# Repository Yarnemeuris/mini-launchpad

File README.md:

# mini-launchpad

Mini launchpad is a midi devicde and control surface for Ableton. When connected to a computer it can: send midi notes, start and stop clips, be used as audio output, change the volume and change paramaters. When not connected to a computer it can: play notes and create sound with a synth.

## connected to Ableton

Mini launchpad is specificy designed to be used with Ableton Live. When you connect it to a computer, it uses an internal usb hub so you can use it as an audio output and send commands through Ableton. When connected it can be used as a midi keyboard or start and stop cilps in the session view.

## standalone

When mini launchpad is in standalone mode, you can only use the midi keyboard. This will send midi into a synthesizer, which will then play sound. The syth can be customized a bit via the encoders at the top, but you can customize it fully if you reprogram the pi.

## compontents

Mini Launchpad has an 8x8 grid of buttons, wired to 4 io expanders. There are also 8 encoders connected to another io expander. The io expanders are used so that the microcontroller doesn't have to poll for changes, but that it can use interupts instead. This way every button press will be registerd and you can press every button at the same time. There are also some extra controll buttons and lights that are wired directly to the microcontroller. But these will also use interupt.

For audio there is a PCM5100 I²S DAC. This will convert the digital audio to a line output. Then there is an amplifier that amplifies the sound. You can also just use the line out.

## playing notes

Actually playing notes is a big part of the luanchpad. There are 2 ways to do this.
- Option 1 is that the notes are layed out linearly. This means that in the bottom left corner is a C, moving right goes up a note and moving up goes up an octave. You can change the octave of the rows by moving up and down. This is also the default option when the launchpad boots up. It looks like this:

- Option 2 is for the notes to be layed out in a c scale. The bottom left note is still a C and going right still goes up a note. But going up goes up a fourth instead of an octave. This layout is the default layout on the Ableton Push and lloks like this:

## progress

The current progress.

- [x] Design the schematic.
- [x] Design the pcb.
- [x] Design the case.
- [x] Write the firmware.

I know not a lot of the features I talk about aren't implemented yet. But for SoM those won't be included. This is beacuse mini midi magic started pretty late and it doesn't really have an end date yet. So by the end of mini midi magic this will all be implemented. The current features that aren't implemented are:
- Connecting to Ableton Live.
- Playing and controlling things in Ableton Live.
- Having a more complex and better synthesizer.
- Being able to change the synthesizer.
- Using the launchpad as an audio interface.
- And I might even add more features.

  I am also unsure if any of the code works and if the case is fully correct. Because I don't have the physical board myself. This will also change before the end of mini midi magic.

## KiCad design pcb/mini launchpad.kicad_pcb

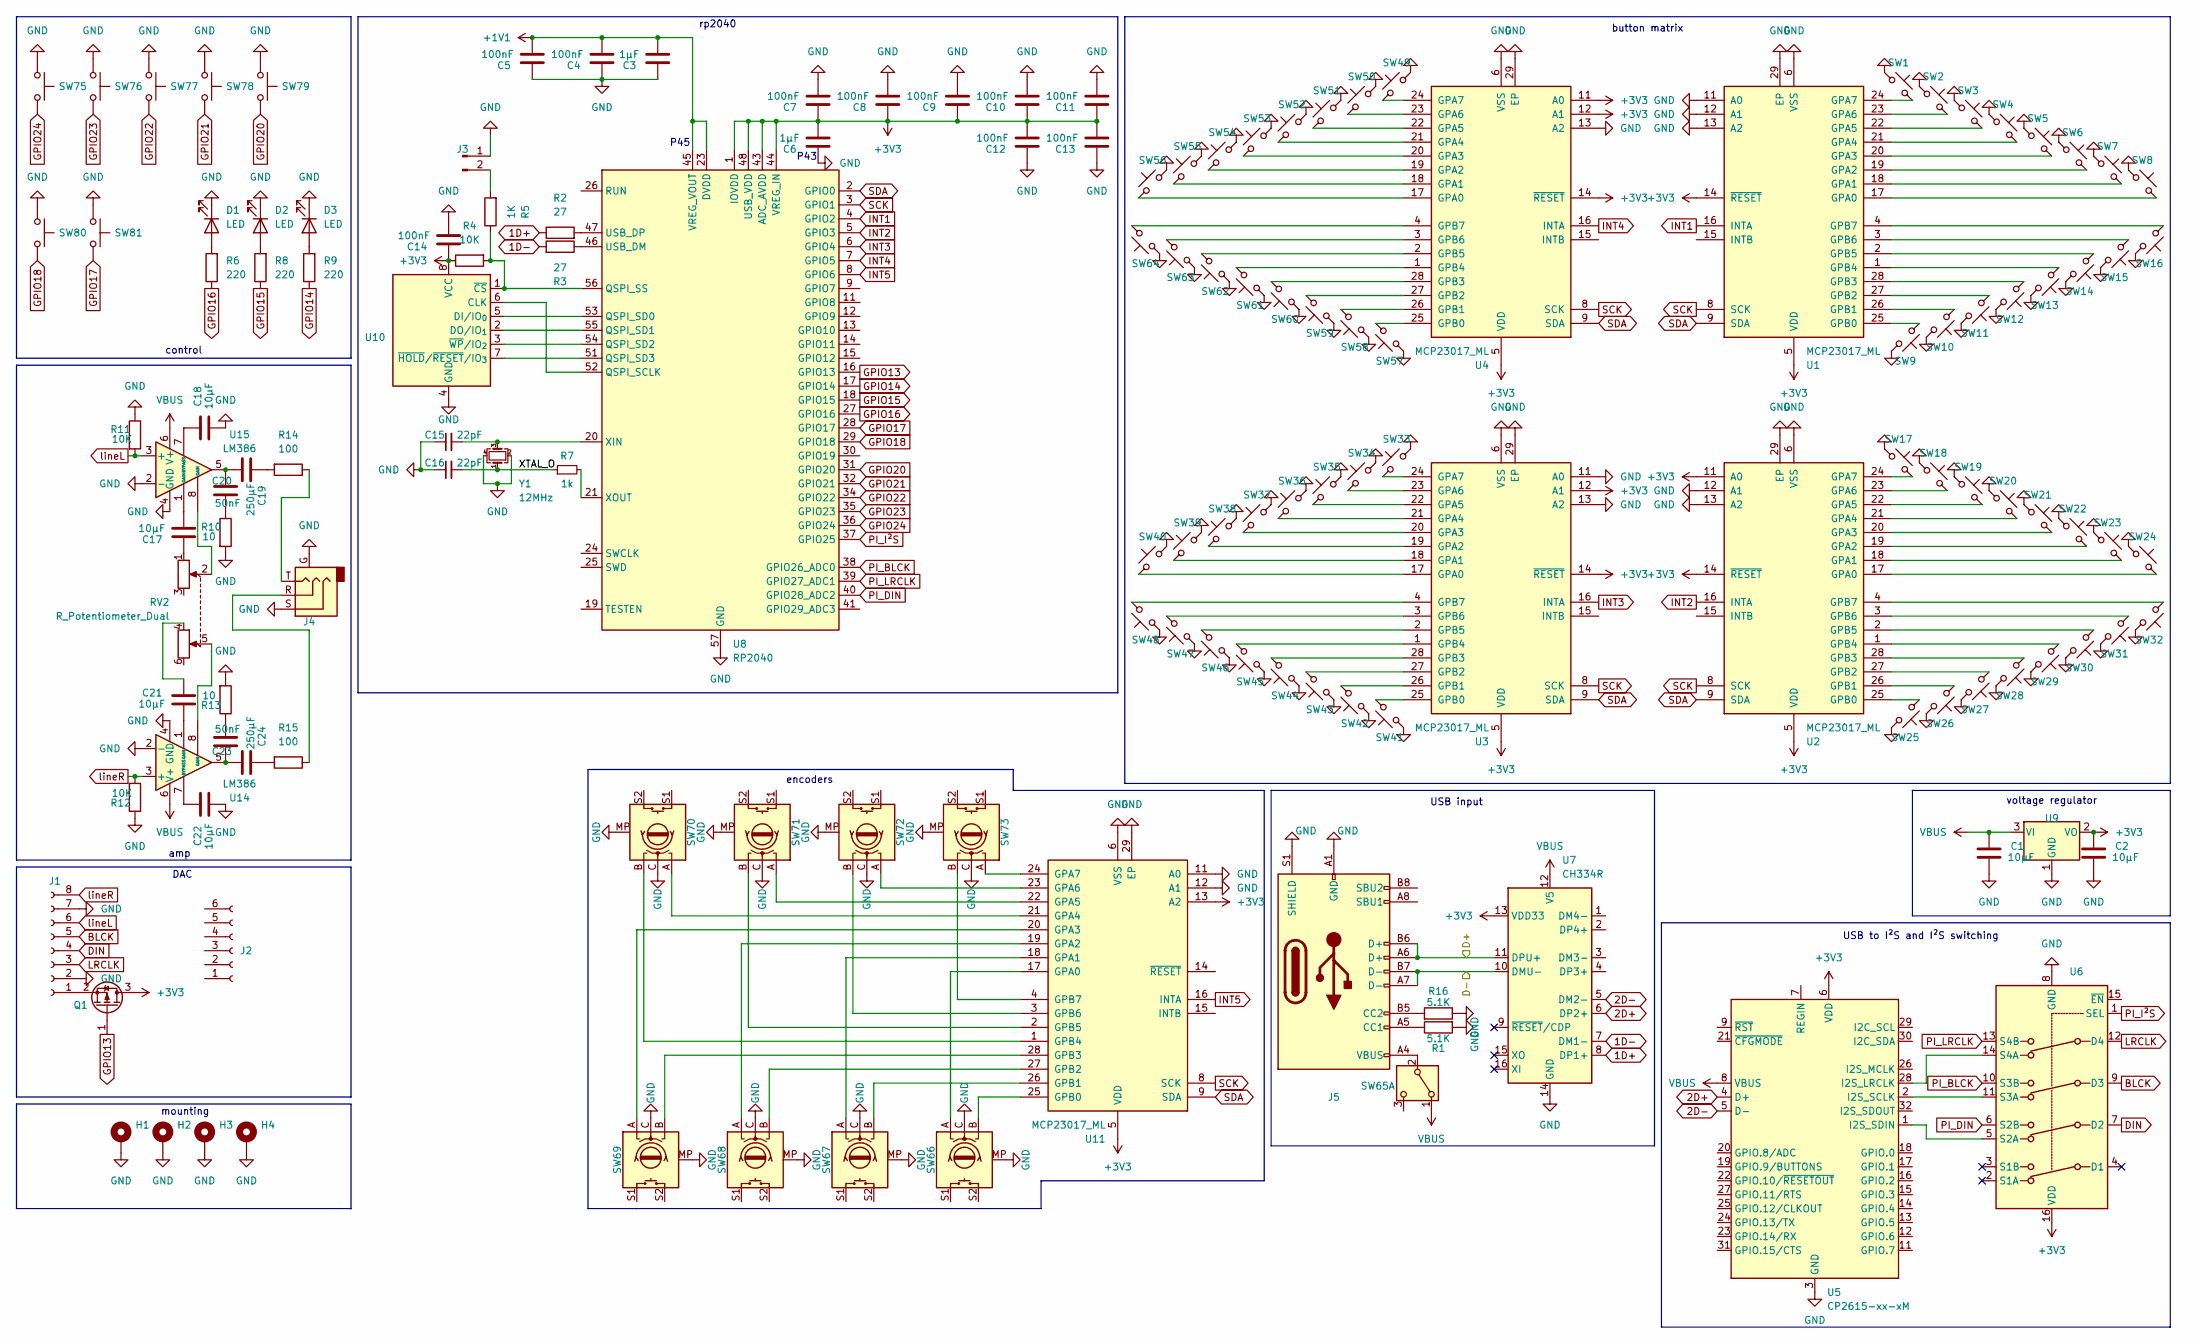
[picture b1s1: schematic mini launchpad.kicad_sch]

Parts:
C1, C2, C17, C18, C21, C22: 10µF; C_0805_2012Metric; LCSC Part C15850
C3, C6: 1µF; C_0805_2012Metric; LCSC Part C28323
C4, C5, C7, C8, C9, C10, C11, C12, C13, C14: 100nF; C_0805_2012Metric; LCSC Part C476766
C15, C16: 22pF; C_0805_2012Metric; LCSC C1804
C19, C24: 250µF; C_1206_3216Metric; LCSC Part C412252
C20, C23: 50nF; C_0805_2012Metric; LCSC Part C107154
D1, D2, D3: LED; LED_D3.0mm; LCSC Part C3028820
H1, H2, H3, H4: MountingHole_Pad; MountingHole_3.2mm_M3_Pad_TopOnly
J1: Conn_01x08_Socket; PinHeader_1x08_P2.54mm_Vertical; LCSC part C492407
J2: Conn_01x06_Socket; PinHeader_1x06_P2.54mm_Vertical; LCSC Part C5383115
J3: Conn_01x02_Pin; PinHeader_1x02_P2.54mm_Horizontal; LCSC Part C42431827
J4: AudioJack3_Ground; Jack_3.5mm_CUI_SJ1-3524N_Horizontal; LCSC Part C4992816
J5: USB_C_Receptacle_USB2.0_16P; USB_C_Receptacle_G-Switch_GT-USB-7010ASV; LCSC Part C2988369
Q1: AO3401A; SOT-23; LCSC Part C15127
R1, R16: 5.1K; R_0402_1005Metric; LCSC Part C105872
R2, R3: 27; R_0402_1005Metric; LCSC Part C138021
R4, R11, R12: 10K; R_0402_1005Metric
R5: 1K; R_0402_1005Metric; LCSC Part C11702
R6, R8, R9: 220; R_0402_1005Metric; LCSC Part C112291
R7: 1k; R_0402_1005Metric; LCSC C11702
R10, R13: 10; R_0402_1005Metric; LCSC Part C138066
R14, R15: 100; R_0402_1005Metric; LCSC Part C106232
RV2: R_Potentiometer_Dual; Potentiometer_Alpha_RD902F-40-00D_Dual_Vertical; LCSC Part C470285
SW1, SW2, SW3, SW4, SW5, SW6, SW7, SW8, SW9, SW10, SW11, SW12, SW13, SW14, SW15, SW16, SW17, SW18, SW19, SW20, SW21, SW22, SW23, SW24, SW25, SW26, SW27, SW28, SW29, SW30, SW31, SW32, SW33, SW34, SW35, SW36, SW37, SW38, SW39, SW40, SW41, SW42, SW43, SW44, SW45, SW46, SW47, SW48, SW49, SW50, SW51, SW52, SW53, SW54, SW55, SW56, SW57, SW58, SW59, SW60, SW61, SW62, SW63, SW64: SW_Cherry_MX_1.00u_PCB
SW65: SW_DPDT_x2; SW_E-Switch_EG2219_DPDT_Angled; LCSC Part C2848873
SW66, SW67, SW68, SW69, SW70, SW71, SW72, SW73: RotaryEncoder_Switch_MP; RotaryEncoder_Alps_EC11E-Switch_Vertical_H20mm_MountingHoles; LCSC Part C202365
SW75, SW76, SW77, SW78, SW79, SW80, SW81: SW_Push; SW_Cherry_MX_1.00u_PCB
U1, U2, U3, U4, U11: MCP23017_ML; QFN-28-1EP_6x6mm_P0.65mm_EP4.25x4.25mm; LCSC Part C639770
U5: CP2615-xx-xM; QFN-32-1EP_5x5mm_P0.5mm_EP3.3x3.3mm; LCSC Part C1521596
U6: TMUX1574PW; TSSOP-16_4.4x5mm_P0.65mm; LCSC Part C2673443
U7: CH334R; QSOP-16_3.9x4.9mm_P0.635mm; LCSC Part C4154405
U8: RP2040; QFN-56-1EP_7x7mm_P0.4mm_EP3.2x3.2mm; LCSC Part C2040
U9: NCP1117-3.3_TO252; TO-252-2; LCSC Part C154606
U10: W25Q128JVS; SOIC-8_5.3x5.3mm_P1.27mm; LCSC Part C97521
U14, U15: LM386; SOIC-8_3.9x4.9mm_P1.27mm; LCSC Part C23573
Y1: 12MHz; Crystal_SMD_3225-4Pin_3.2x2.5mm; LCSC Part C9002

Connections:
1D+: R2.1, U7.8 (DP1+)
1D-: R3.2, U7.7 (DM1-)
2D+: U5.4 (D+), U7.6 (DP2+)
2D-: U5.5 (D-), U7.5 (DM2-)
+1V1: C3.1, C4.1, C5.1, U8.23 (DVDD), U8.45 (VREG_VOUT), U8.50 (DVDD)
+3V3: C2.2, C6.1, C7.2, C8.2, C9.2, C10.2, C11.2, C12.1, C13.1, C14.2, Q1.3 (D), R4.1, U1.5 (VDD), U1.14 (~RESET), U2.5 (VDD), U2.11 (A0), U2.14 (~RESET), U3.5 (VDD), U3.12 (A1), U3.14 (~RESET), U4.5 (VDD), U4.11 (A0), U4.12 (A1), U4.14 (~RESET), U5.6 (VDD), U6.16 (VDD), U7.13 (VDD33), U8.1 (IOVDD), U8.10 (IOVDD), U8.22 (IOVDD), U8.33 (IOVDD), U8.42 (IOVDD), U8.43 (ADC_AVDD), U8.44 (VREG_IN), U8.48 (USB_VDD), U8.49 (IOVDD), U9.2 (VO), U10.8 (VCC), U11.5 (VDD), U11.13 (A2)
/D+: J5.A6 (D+), J5.B6 (D+), U7.11 (DPU+)
/D-: J5.A7 (D-), J5.B7 (D-), U7.10 (DMU-)
/XTAL_O: C16.2, R7.1, Y1.1
BLCK: J1.5, U6.9 (D3)
DIN: J1.4, U6.7 (D2)
GND: C1.1, C2.1, C3.2, C4.2, C5.2, C6.2, C7.1, C8.1, C9.1, C10.1, C11.1, C12.2, C13.2, C14.1, C15.1, C16.1, C18.1, C22.1, D1.1 (K), D2.1 (K), D3.1 (K), H1.1, H2.1, H3.1, H4.1, J1.2, J1.7, J3.1, J4.G, J4.S, J5.A1 (GND), J5.A12 (GND), J5.B1 (GND), J5.B12 (GND), J5.S1 (SHIELD), R1.2, R10.2, R11.1, R12.1, R13.2, R16.1, SW1.1, SW2.1, SW3.1, SW4.1, SW5.1, SW6.1, SW7.1, SW8.1, SW9.1, SW10.1, SW11.1, SW12.1, SW13.1, SW14.1, SW15.1, SW16.1, SW17.1, SW18.1, SW19.1, SW20.1, SW21.1, SW22.1, SW23.1, SW24.1, SW25.1, SW26.1, SW27.1, SW28.1, SW29.1, SW30.1, SW31.1, SW32.1, SW33.1, SW34.1, SW35.1, SW36.1, SW37.1, SW38.1, SW39.1, SW40.1, SW41.1, SW42.1, SW43.1, SW44.1, SW45.1, SW46.1, SW47.1, SW48.1, SW49.1, SW50.1, SW51.1, SW52.1, SW53.1, SW54.1, SW55.1, SW56.1, SW57.1, SW58.1, SW59.1, SW60.1, SW61.1, SW62.1, SW63.1, SW64.1, SW66.C, SW66.MP, SW67.C, SW67.MP, SW68.C, SW68.MP, SW69.C, SW69.MP, SW70.C, SW70.MP, SW71.C, SW71.MP, SW72.C, SW72.MP, SW73.C, SW73.MP, SW75.1, SW76.1, SW77.1, SW78.1, SW79.1, SW80.1, SW81.1, U1.6 (VSS), U1.11 (A0), U1.12 (A1), U1.13 (A2), U1.29 (EP), U2.6 (VSS), U2.12 (A1), U2.13 (A2), U2.29 (EP), U3.6 (VSS), U3.11 (A0), U3.13 (A2), U3.29 (EP), U4.6 (VSS), U4.13 (A2), U4.29 (EP), U5.3 (GND), U5.33 (GND), U6.8 (GND), U7.14 (GND), U8.57 (GND), U9.1 (GND), U10.4 (GND), U11.6 (VSS), U11.11 (A0), U11.12 (A1), U11.29 (EP), U14.2 (-), U14.4 (GND), U15.2 (-), U15.4 (GND), Y1.2, Y1.4
GPIO13: Q1.1 (G), U8.16 (GPIO13)
GPIO14: R9.1, U8.17 (GPIO14)
GPIO15: R8.1, U8.18 (GPIO15)
GPIO16: R6.1, U8.27 (GPIO16)
GPIO17: SW81.2, U8.28 (GPIO17)
GPIO18: SW80.2, U8.29 (GPIO18)
GPIO20: SW79.2, U8.31 (GPIO20)
GPIO21: SW78.2, U8.32 (GPIO21)
GPIO22: SW77.2, U8.34 (GPIO22)
GPIO23: SW76.2, U8.35 (GPIO23)
GPIO24: SW75.2, U8.36 (GPIO24)
INT1: U1.16 (INTA), U8.4 (GPIO2)
INT2: U2.16 (INTA), U8.5 (GPIO3)
INT3: U3.16 (INTA), U8.6 (GPIO4)
INT4: U4.16 (INTA), U8.7 (GPIO5)
INT5: U8.8 (GPIO6), U11.16 (INTA)
LRCLK: J1.3, U6.12 (D4)
unnamed: C17.1, U15.1 (GAIN)
unnamed: C17.2, RV2.1
unnamed: C19.1, C20.1, U15.5
unnamed: C19.2, R14.2
unnamed: C20.2, R10.1
unnamed: C21.1, U14.1 (GAIN)
unnamed: C21.2, RV2.4
unnamed: C23.1, C24.1, U14.5
unnamed: C23.2, R13.1
unnamed: C24.2, R15.2
unnamed: D1.2 (A), R6.2
unnamed: D2.2 (A), R8.2
unnamed: D3.2 (A), R9.2
unnamed: J1.1, Q1.2 (S)
unnamed: J3.2, R5.2
unnamed: J4.R, R15.1
unnamed: J4.T, R14.1
unnamed: J5.A5 (CC1), R1.1
unnamed: J5.B5 (CC2), R16.2
unnamed: RV2.2, U15.8 (GAIN)
unnamed: RV2.5, U14.8 (GAIN)
unnamed: J5.A4 (VBUS), J5.A9 (VBUS), J5.B4 (VBUS), J5.B9 (VBUS), SW65.2 (B)
unnamed: SW8.2, U1.17 (GPA0)
unnamed: SW7.2, U1.18 (GPA1)
unnamed: SW6.2, U1.19 (GPA2)
unnamed: SW5.2, U1.20 (GPA3)
unnamed: SW4.2, U1.21 (GPA4)
unnamed: SW3.2, U1.22 (GPA5)
unnamed: SW2.2, U1.23 (GPA6)
unnamed: SW1.2, U1.24 (GPA7)
unnamed: SW9.2, U1.25 (GPB0)
unnamed: SW10.2, U1.26 (GPB1)
unnamed: SW11.2, U1.27 (GPB2)
unnamed: SW12.2, U1.28 (GPB3)
unnamed: SW13.2, U1.1 (GPB4)
unnamed: SW14.2, U1.2 (GPB5)
unnamed: SW15.2, U1.3 (GPB6)
unnamed: SW16.2, U1.4 (GPB7)
unnamed: SW24.2, U2.17 (GPA0)
unnamed: SW23.2, U2.18 (GPA1)
unnamed: SW22.2, U2.19 (GPA2)
unnamed: SW21.2, U2.20 (GPA3)
unnamed: SW20.2, U2.21 (GPA4)
unnamed: SW19.2, U2.22 (GPA5)
unnamed: SW18.2, U2.23 (GPA6)
unnamed: SW17.2, U2.24 (GPA7)
unnamed: SW25.2, U2.25 (GPB0)
unnamed: SW26.2, U2.26 (GPB1)
unnamed: SW27.2, U2.27 (GPB2)
unnamed: SW28.2, U2.28 (GPB3)
unnamed: SW29.2, U2.1 (GPB4)
unnamed: SW30.2, U2.2 (GPB5)
unnamed: SW31.2, U2.3 (GPB6)
unnamed: SW32.2, U2.4 (GPB7)
unnamed: SW40.2, U3.17 (GPA0)
unnamed: SW39.2, U3.18 (GPA1)
unnamed: SW38.2, U3.19 (GPA2)
unnamed: SW37.2, U3.20 (GPA3)
unnamed: SW36.2, U3.21 (GPA4)
unnamed: SW35.2, U3.22 (GPA5)
unnamed: SW34.2, U3.23 (GPA6)
unnamed: SW33.2, U3.24 (GPA7)
unnamed: SW41.2, U3.25 (GPB0)
unnamed: SW42.2, U3.26 (GPB1)
unnamed: SW43.2, U3.27 (GPB2)
unnamed: SW44.2, U3.28 (GPB3)
unnamed: SW45.2, U3.1 (GPB4)
unnamed: SW46.2, U3.2 (GPB5)
unnamed: SW47.2, U3.3 (GPB6)
unnamed: SW48.2, U3.4 (GPB7)
unnamed: SW56.2, U4.17 (GPA0)
unnamed: SW55.2, U4.18 (GPA1)
unnamed: SW54.2, U4.19 (GPA2)
unnamed: SW53.2, U4.20 (GPA3)
unnamed: SW52.2, U4.21 (GPA4)
unnamed: SW51.2, U4.22 (GPA5)
unnamed: SW50.2, U4.23 (GPA6)
unnamed: SW49.2, U4.24 (GPA7)
unnamed: SW57.2, U4.25 (GPB0)
unnamed: SW58.2, U4.26 (GPB1)
unnamed: SW59.2, U4.27 (GPB2)
unnamed: SW60.2, U4.28 (GPB3)
unnamed: SW61.2, U4.1 (GPB4)
unnamed: SW62.2, U4.2 (GPB5)
unnamed: SW63.2, U4.3 (GPB6)
unnamed: SW64.2, U4.4 (GPB7)
unnamed: U5.28 (I2S_LRCLK), U6.14 (S4A)
unnamed: U5.2 (I2S_SCLK), U6.11 (S3A)
unnamed: U5.1 (I2S_SDIN), U6.5 (S2A)
unnamed: R3.1, U8.46 (USB_DM)
unnamed: R2.2, U8.47 (USB_DP)
unnamed: C15.2, U8.20 (XIN), Y1.3
unnamed: R7.2, U8.21 (XOUT)
unnamed: U8.52 (QSPI_SCLK), U10.6 (CLK)
unnamed: U8.53 (QSPI_SD0), U10.5 (DI/IO_{0})
unnamed: U8.55 (QSPI_SD1), U10.2 (DO/IO_{1})
unnamed: R4.2, R5.1, U8.56 (QSPI_SS), U10.1 (~CS)
unnamed: U8.51 (QSPI_SD3), U10.7 (~HOLD/~RESET/IO_{3})
unnamed: U8.54 (QSPI_SD2), U10.3 (~WP/IO_{2})
unnamed: SW66.A, U11.17 (GPA0)
unnamed: SW67.A, U11.18 (GPA1)
unnamed: SW68.A, U11.19 (GPA2)
unnamed: SW69.A, U11.20 (GPA3)
unnamed: SW70.A, U11.21 (GPA4)
unnamed: SW71.A, U11.22 (GPA5)
unnamed: SW72.A, U11.23 (GPA6)
unnamed: SW73.A, U11.24 (GPA7)
unnamed: SW66.B, U11.25 (GPB0)
unnamed: SW67.B, U11.26 (GPB1)
unnamed: SW68.B, U11.27 (GPB2)
unnamed: SW69.B, U11.28 (GPB3)
unnamed: SW70.B, U11.1 (GPB4)
unnamed: SW71.B, U11.2 (GPB5)
unnamed: SW72.B, U11.3 (GPB6)
unnamed: SW73.B, U11.4 (GPB7)
unnamed: C22.2, U14.7 (BYPASS)
unnamed: C18.2, U15.7 (BYPASS)
PI_BLCK: U6.10 (S3B), U8.38 (GPIO26_ADC0)
PI_DIN: U6.6 (S2B), U8.40 (GPIO28_ADC2)
PI_I²S: U6.1 (SEL), U8.37 (GPIO25)
PI_LRCLK: U6.13 (S4B), U8.39 (GPIO27_ADC1)
SCK: U1.8 (SCK), U2.8 (SCK), U3.8 (SCK), U4.8 (SCK), U8.3 (GPIO1), U11.8 (SCK)
SDA: U1.9 (SDA), U2.9 (SDA), U3.9 (SDA), U4.9 (SDA), U8.2 (GPIO0), U11.9 (SDA)
VBUS: C1.2, SW65.1 (A), U5.8 (VBUS), U7.12 (V5), U9.3 (VI), U14.6 (V+), U15.6 (V+)
lineL: J1.6, R11.2, U15.3 (+)
lineR: J1.8, R12.2, U14.3 (+)

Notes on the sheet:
rp2040
button matrix
USB to I²S and I²S switching
P43
control
amp
mounting
DAC
encoders
USB input
voltage regulator
P45

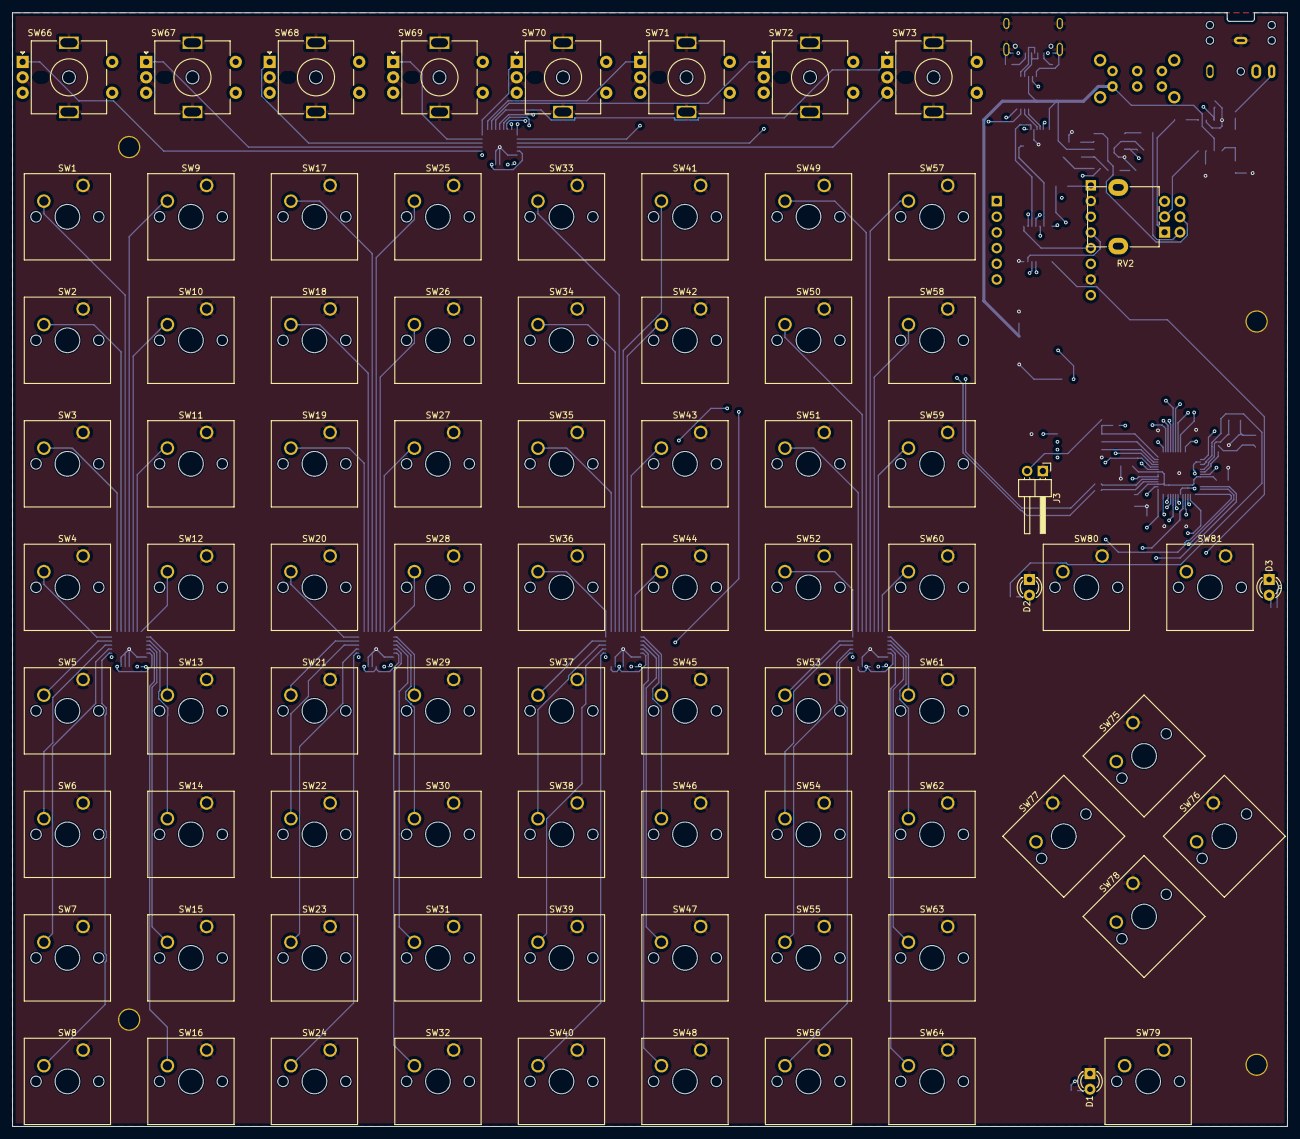
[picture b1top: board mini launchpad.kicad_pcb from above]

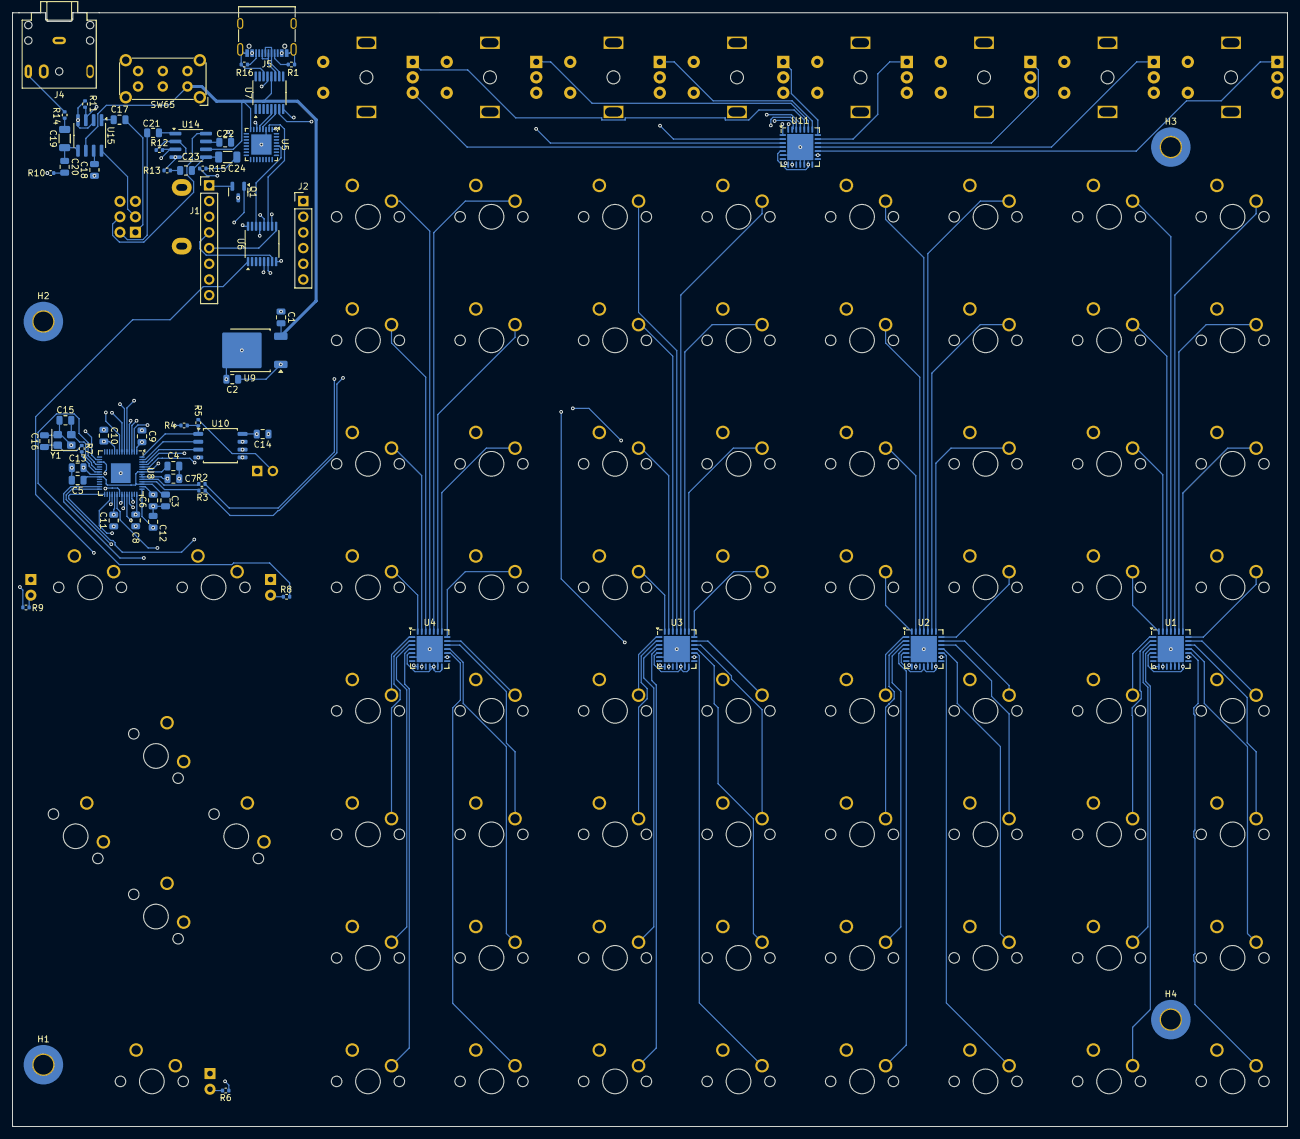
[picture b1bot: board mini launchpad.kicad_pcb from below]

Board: 4 copper layers, 206.5 x 180.3 mm, 148 parts (64 on the bottom side), 155 nets.

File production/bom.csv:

Designator,Footprint,Quantity,Value,LCSC Part #
"C1, C17, C18, C2, C21, C22",0805,6,10µF,C15850
"C10, C11, C12, C13, C14, C4, C5, C7, C8, C9",0805,10,100nF,C476766
"C15, C16",0805,2,22pF,C1804
C19,1206,1,250µF,
"C20, C23",0805,2,50nF,C107154
C24,1206,1,250µF,C412252
"C3, C6",0805,2,1µF,C28323
"D1, D2, D3",LED_D3.0mm,3,LED,C3028820
J1,PinHeader_1x08_P2.54mm_Vertical,1,Conn_01x08_Socket,
J2,PinHeader_1x06_P2.54mm_Vertical,1,Conn_01x06_Socket,C5383115
J4,Jack_3.5mm_CUI_SJ1-3524N_Horizontal,1,AudioJack3_Ground,C4992816
J5,USB_C_Receptacle_G-Switch_GT-USB-7010ASV,1,USB_C_Receptacle_USB2.0_16P,C2988369
Q1,SOT-23,1,AO3401A,C15127
"R1, R16",0402,2,5.1K,C105872
"R10, R13",0402,2,10,C138066
"R11, R12, R4",0402,3,10K,
"R14, R15",0402,2,100,C106232
"R2, R3",0402,2,27,C138021
"R5, R7",0402,2,1K,C11702
"R6, R8, R9",0402,3,220,C112291
RV2,Potentiometer_Alpha_RD902F-40-00D_Dual_Vertical,1,R_Potentiometer_Dual,C470285
"SW1, SW10, SW11, SW12, SW13, SW14, SW15, SW16, SW17, SW18, SW19, SW2, SW20, SW21, SW22, SW23, SW24, SW25, SW26, SW27, SW28, SW29, SW3, SW30, SW31, SW32, SW33, SW34, SW35, SW36, SW37, SW38, SW39, SW4, SW40, SW41, SW42, SW43, SW44, SW45, SW46, SW47, SW48, SW49, SW5, SW50, SW51, SW52, SW53, SW54, SW55, SW56, SW57, SW58, SW59, SW6, SW60, SW61, SW62, SW63, SW64, SW7, SW8, SW9",SW_Cherry_MX_1.00u_PCB,64,~,
SW65,SW_E-Switch_EG2219_DPDT_Angled,1,SW_DPDT_x2,C2848873
"SW66, SW67, SW68, SW69, SW70, SW71, SW72, SW73",RotaryEncoder_Alps_EC11E-Switch_Vertical_H20mm_MountingHoles,8,RotaryEncoder_Switch_MP,C202365
"SW75, SW76, SW77, SW78, SW79, SW80, SW81, SW83",SW_Cherry_MX_1.00u_PCB,8,SW_Push,
"U1, U11, U2, U3, U4",QFN-28-1EP_6x6mm_P0.65mm_EP4.25x4.25mm,5,MCP23017_ML,C639770
U10,SOIC-8_5.3x5.3mm_P1.27mm,1,W25Q128JVS,C97521
"U14, U15",SOIC-8_3.9x4.9mm_P1.27mm,2,LM386,C23573
U5,QFN-32-1EP_5x5mm_P0.5mm_EP3.3x3.3mm,1,CP2615-xx-xM,C1521596
U6,TSSOP-16_4.4x5mm_P0.65mm,1,TMUX1574PW,C2673443
U7,QSOP-16_3.9x4.9mm_P0.635mm,1,CH334R,C4154405
U8,QFN-56-1EP_7x7mm_P0.4mm_EP3.2x3.2mm,1,RP2040,C2040
U9,TO-252-2,1,NCP1117-3.3_TO252,C154606
Y1,Crystal_SMD_3225-4Pin_3.2x2.5mm,1,12MHz,C9002

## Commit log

2025-09-06 added pcb
2025-09-06 journal uodate
2025-09-06 pcb update
2025-09-07 journal update
2025-09-07 schematic update
2025-09-08 journal update 8/9/2025
2025-09-11 journal update 11/9/2025
2025-09-13 journal update 13/9/2025
2025-09-14 journal update 14/9/2025
2025-09-15 journal update 15/9/2025
2025-09-16 journal update 16/9/2025
2025-09-17 journal update 17/9/2025
2025-09-18 journal update 18/9/2025
2025-09-20 journal update 20/9/2025
2025-09-21 journal update 21/9/2025
2025-09-22 journal update 22/9/2025
2025-09-22 this time I swear it's the final pcb update
2025-09-23 journal update 23/9/2025
2025-09-24 journal update 24/9/2025
2025-09-24 folder changes firmware not working for me currently
2025-09-24 fixed the journal days
2025-09-25 journal update 25/09/2025
2025-09-30 journal update 30/9/2025
2025-09-30 basic code
2025-10-01 Code to make sound from button presses.
2025-10-01 added a second layout
2025-10-01 README update
2025-10-01 added images to README
2025-10-01 added to README what features aren't implemented.
2025-10-01 journal update 1/10/2025
